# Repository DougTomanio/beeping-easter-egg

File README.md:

# Beeping Easter Egg 🥚🔊

## Generate fabrication files
```
docker run --rm -v ${PWD}:/app -e COLS=5 -e ROWS=5 kicad/kicad:9.0 bash /app/scripts/generate-fabrication-files.sh
```

## Generate render pngs and schematic svg
```
docker run --rm -v ${PWD}:/app kicad/kicad:9.0 bash /app/scripts/generate-renders-for-readme.sh
```

## KiCad plugins / tools / scripts
* https://github.com/yaqwsx/KiKit
* https://github.com/uPesy/easyeda2kicad.py

## Component calculations
[component-calculations.md](component-calculations.md)

## TODO
* Try KiCad jobset to replace generate-renders-for-readme.sh
* Use official KiKit docker image once it supports KiCad 9
* Find a proper 3D model for switch

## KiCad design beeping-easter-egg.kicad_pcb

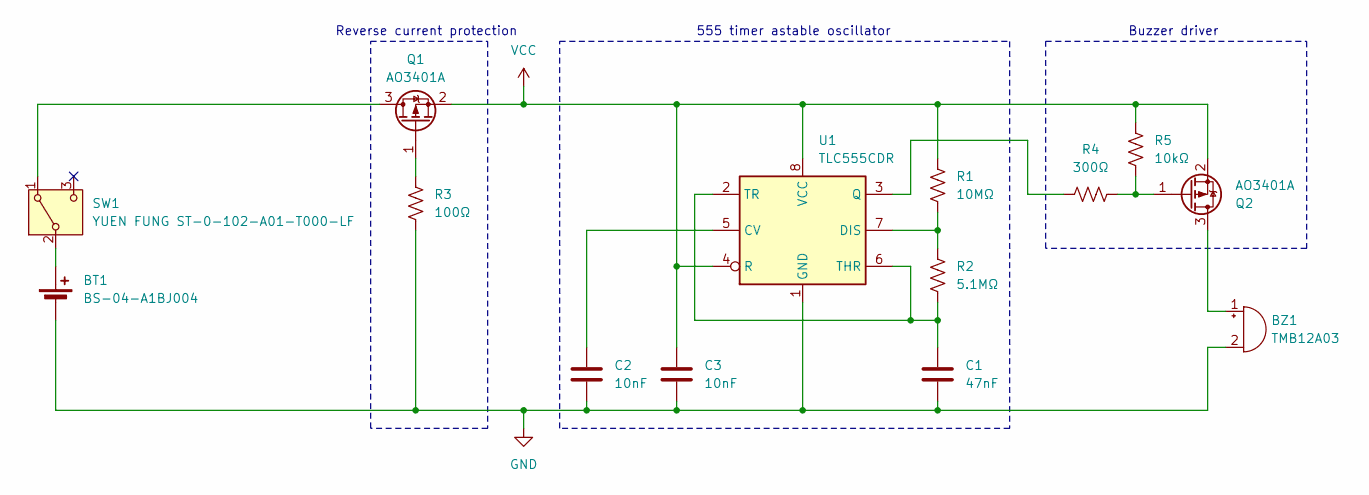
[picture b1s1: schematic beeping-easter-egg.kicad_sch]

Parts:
BT1: BS-04-A1BJ004; BAT-TH_BS-04-A1BJ004; LCSC C964750
BZ1: TMB12A03; Buzzer_12x9.5RM7.6; LCSC C96222
C1: 47nF; C_0603_1608Metric; LCSC C1622
C2, C3: 10nF; C_0603_1608Metric; LCSC C57112
Q1, Q2: AO3401A; SOT-23; LCSC C15127
R1: 10MΩ; R_0603_1608Metric; LCSC C7250
R2: 5.1MΩ; R_0603_1608Metric; LCSC C13320
R3: 100Ω; R_0603_1608Metric; LCSC C22775
R4: 300Ω; R_0603_1608Metric; LCSC C23025
R5: 10kΩ; R_0603_1608Metric; LCSC C25804
SW1: YUEN FUNG ST-0-102-A01-T000-LF; SW-TH_3P-L8.3-W5.2-P2.54_ST-0-102-A01-T000; LCSC C1788487
U1: TLC555CDR; SOIC-8_3.9x4.9mm_P1.27mm; LCSC C6986

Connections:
GND: BT1.2 (-), BZ1.2 (-), C1.2, C2.2, C3.2, R3.2, U1.1 (GND)
unnamed: BT1.1 (+), SW1.2 (B)
unnamed: BZ1.1 (+), Q2.3 (D)
unnamed: Q1.3 (D), SW1.1 (A)
unnamed: Q1.1 (G), R3.1
unnamed: Q2.1 (G), R4.2, R5.2
unnamed: C2.1, U1.5 (CV)
unnamed: R1.2, R2.1, U1.7 (DIS)
unnamed: R4.1, U1.3 (Q)
unnamed: C1.1, R2.2, U1.2 (TR), U1.6 (THR)
VCC: C3.1, Q1.2 (S), Q2.2 (S), R1.1, R5.1, U1.4 (R), U1.8 (VCC)

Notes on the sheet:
Reverse current protection
Buzzer driver
555 timer astable oscillator

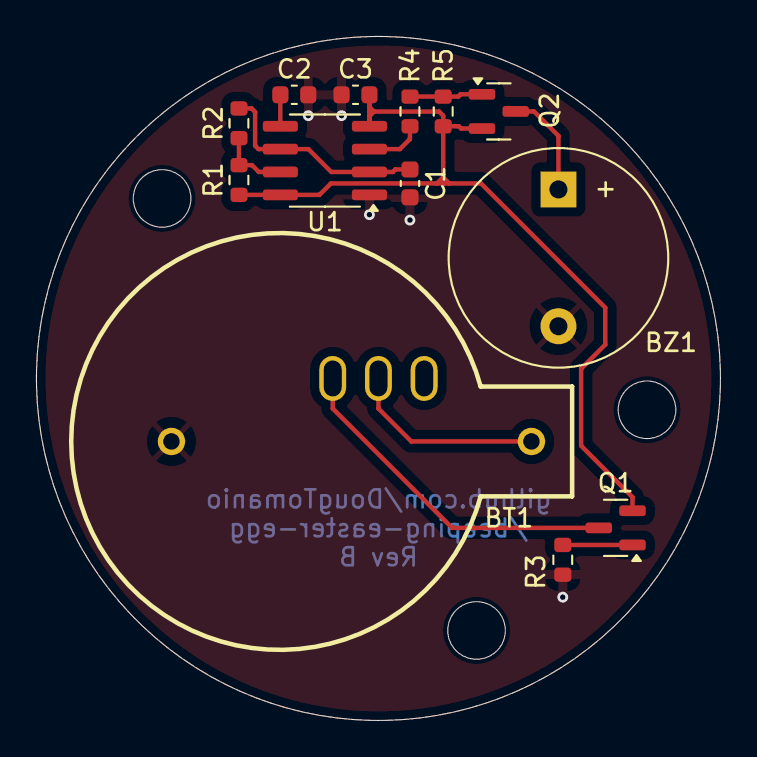
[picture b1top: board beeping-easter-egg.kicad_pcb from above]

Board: 2 copper layers, 38.0 x 38.0 mm, 14 parts (1 on the bottom side), 11 nets.

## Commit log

2025-03-08 Change buzzer driver to pnp, remove 555 inverting buffer.
    Add reverse polarity protection.
    Add custom footprint for battery holder.
2025-03-08 update pcb from schematic
2025-03-08 switch from bjts to mosfets
2025-03-08 Switch to SMD footprints. Add filter cap to reset.
2025-03-08 Change 555 R and C values to reduce current. Ratio and thus timing stays the same. Some component renaming.
2025-03-08 Change 555 R and C values to reduce current. Ratio and thus timing stays the same. Some component renaming. Add LCSC field.
2025-03-08 Revert commit of generated jlcpcb files
    This partially reverts commit 3e110100dbd27910e5bf91a673afcf49d5367dce.
2025-03-08 Revert commit of generated jlcpcb files
    This partially reverts commit 3e110100dbd27910e5bf91a673afcf49d5367dce.
    (cherry picked from commit 4657ed03a1a465b8d6b939ffa78540d57d0fadf1)
2025-03-08 Adjust R1 value to nearest commonly availably value. Add LCSC number for battery holder.
2025-03-08 Convert to kicad version 9. Add LCSC part numbers.
2025-03-08 some schematic cleanup
2025-03-08 Add footprints for battery holder and switch using easyeda2kicad script.
2025-03-08 Place components. Add 3D model for switch.
2025-03-08 routing
2025-03-08 Improved placement of some ground vias
2025-03-08 Clean up fab layers. Update some component info.
2025-03-08 Add readme. Add exported schematic and renders for readme.
2025-03-08 Try to fix LaTeX rendering on github page
2025-03-08 Fix LaTeX rendering in README.md
2025-03-08 Cleanup 555 timing calculations in README.md
2025-03-08 Resize schematic to A5. Add title to schematic.
2025-03-08 Change track width to 0.25mm
2025-03-08 Add tooling holes per jlcpcb's spec
2025-03-08 Add JLCPCB order number placeholder per jlcpcb spec
2025-03-08 Add 3rd tooling hole. Remove unused custom footprint for tooling hole.
2025-03-08 update renders
2025-03-08 Fix DRC issues with tooling holes
2025-03-08 Add project label to silkscreen
2025-03-08 Ran "Cleanup Tracks & Vias" tool
2025-03-08 Fix missing ref DRC issue with tooling holes
2025-03-08 Move component calculations to separate md file
2025-03-08 Change title silkscreen style to knockout
2025-03-08 Reduce text size of JLCPCB order number placeholder
2025-03-08 Use docker for generation of renders and fabrication files. Add some todos to the readme.
2025-03-08 Move component info generated by easyeda2kicad to local project library.
2025-03-08 Fix DRC issue with tooling holes
2025-03-08 Remove finished todo from README.md
2025-03-08 Add project specific library to configuration
2025-03-08 Clean up ground plane zone border
2025-03-08 Add a folder for renders
2025-03-08 panelization with kikit
2025-03-09 Add some todos to README.md
2025-03-09 Make sure we are running in the kicad docker container before doing kikit setup
2025-03-09 Corrections for JLCPCB component rotation using KiKit "JLCPCB_CORRECTION" property
2025-03-09 Use JLCPCB spec 3.85mm offset for fiducials. Switch to frame style rails. Switch to 3 fiducials for non symmetrical pattern.
2025-03-09 Move scripts into a folder
2025-03-09 Remove completed todo
2025-03-09 Set solder mask clearances per jlcpcb spec
2025-03-09 Add env vars for panelization rows and cols
2025-03-09 Update pcb from schematic to pull in missing JLCPCB_CORRECTION fields
2025-03-09 Remove tooling holes. They are added to the panelization frame instead.
2025-03-09 Remove jlc order number placeholder. It is added to the panelization frame instead.
2025-03-09 Move label to back copper. Add Rev number.
2025-03-09 Remove reference to unused KiCad plugin. Using KiKit to generate fab files instead.
2025-03-09 Hide JLCPCB_CORRECTION field on schematic.
2025-03-09 Set title
2025-03-09 Use jlcpcb spec for tooling holes. Changed panelization frame type to tightframe.
2025-03-11 Fix mistake in timing calculations.
2025-03-11 Update component values to reflect corrected timing calculations
2025-03-11 update rev
2025-03-12 Add cover panel
2025-03-12 Mark mounting holes as excluded from schematic.
2025-03-12 Add another mounting hole for cover plate. Move Q1 and R3 to make room for new mounting hole.
2025-03-12 Change panelization rows and cols defaults to maximum without incuring large board fees from jlc.
2025-03-14 Separate cover into separate kicad_pcb file.
2025-03-14 Update title
2025-03-14 update readme with new default panelization rows/cols
2025-03-14 Reorder cols/rows to match JLCPCB site to avoid confusion when ordering
2025-03-14 Adjust thermal reliefs for through-hole components
2025-03-14 Fix panelization script issue
2025-03-14 Adjust panelization spacing
2025-03-14 Add generated fabrication files to gitignore
